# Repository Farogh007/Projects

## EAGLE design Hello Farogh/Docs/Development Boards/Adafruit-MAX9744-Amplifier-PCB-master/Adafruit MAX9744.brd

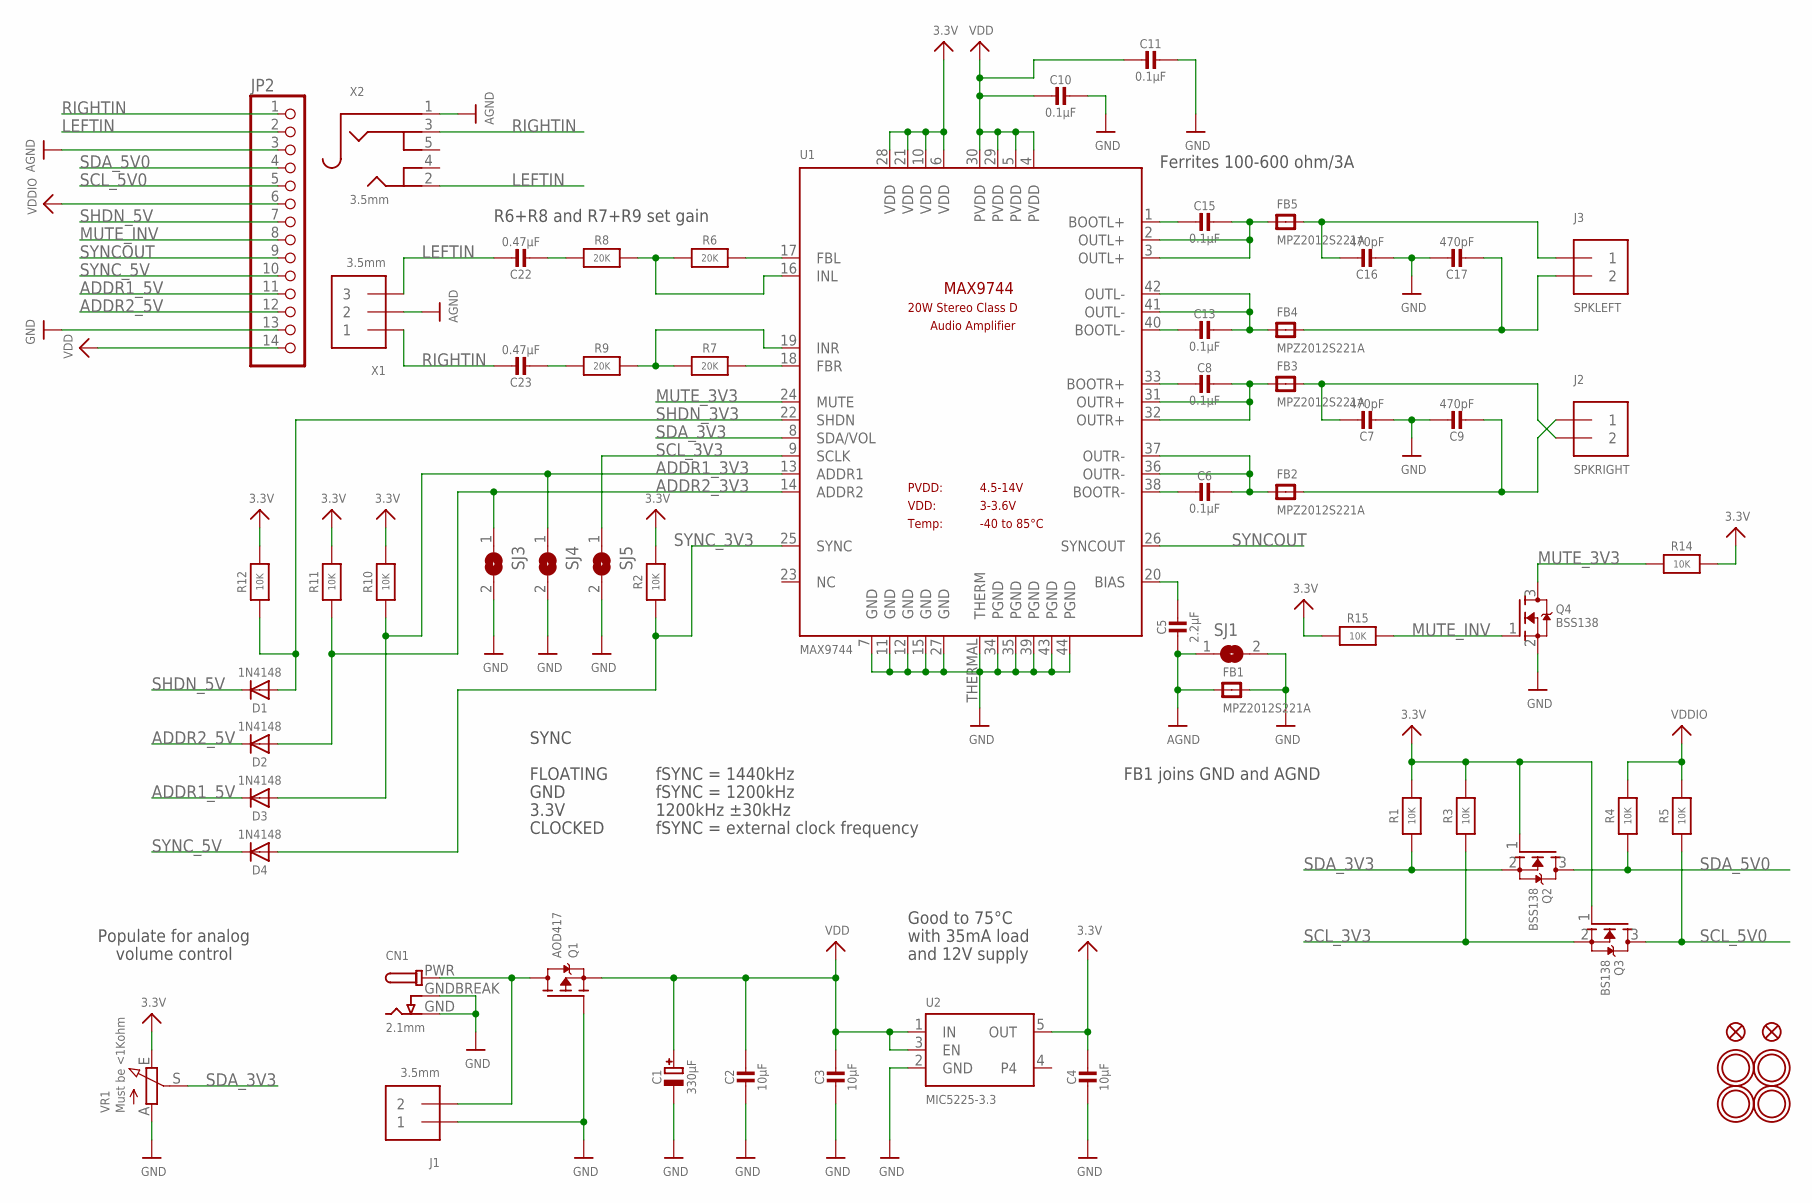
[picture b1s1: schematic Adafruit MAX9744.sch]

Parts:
C1: 330µF; CELEC_3.5MM_8MM
C2, C3, C4: 10µF; 0805-NO
C5: 2.2µF; 0805-NO
C6, C8, C10, C11, C13, C15: 0.1µF; 0805-NO
C7, C9, C16, C17: 470pF; 0805-NO
C22, C23: 0.47µF; 0805-NO
CN1: 2.1mm; DCJACK_2MM_SMT
D1, D2, D3, D4: 1N4148; SOD-323
FB1, FB2, FB3, FB4, FB5: MPZ2012S221A; _0805
FID1, FID2: FIDUCIAL""; FIDUCIAL_1MM
J1: 3.5mm; TERMBLOCK_1X2-3.5MM
J2: SPKRIGHT; TERMBLOCK_1X2-3.5MM
J3: SPKLEFT; TERMBLOCK_1X2-3.5MM
JP2: HEADER-1X14; 1X14_ROUND70
Q1: AOD417; TO252
Q2, Q4: BSS138; SOT23-WIDE
Q3: BS138; SOT23-WIDE
R1, R3, R4, R5, R12: 10K; 0805-NO
R2, R10, R11, R14, R15: 10K; _0805MP
R6, R7, R8, R9: 20K; 0805-NO
SJ1, SJ3, SJ4, SJ5: SOLDERJUMPER; SOLDERJUMPER_ARROW_NOPASTE
U1: MAX9744; TQFN44_7MM
U2: MIC5225-3.3; SOT23-5
U$29, U$38, U$39, U$40: MOUNTINGHOLE2.5_THICK; MOUNTINGHOLE_2.5_PLATED_THICK
VR1: Must be <1Kohm; TRIMPOT_100MILPTH
X1: 3.5mm; TERMBLOCK_1X3-3.5MM
X2: 3.5mm; 4UCONN_19269

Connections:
3.3V: C4.1, Q2.1 (G), Q3.1 (G), R1.2, R2.2, R3.2, R10.2, R11.2, R12.2, R14.2, R15.1, U1.6 (VDD), U1.10 (VDD), U1.21 (VDD), U1.28 (VDD), U2.5 (OUT), VR1.E
ADDR1_3V3: D3.A, R10.1, SJ4.1, U1.13 (ADDR1)
ADDR1_5V: D3.C, JP2.11
ADDR2_3V3: D2.A, R11.1, SJ3.1, U1.14 (ADDR2)
ADDR2_5V: D2.C, JP2.12
AGND: C5.2, FB1.1, JP2.3, SJ1.1, X1.2, X2.1
GND: C1.-, C2.2, C3.2, C4.2, C7.2, C9.1, C10.1, C11.1, C16.2, C17.1, CN1.GND, CN1.GNDBREAK, FB1.2, J1.1, JP2.13, Q1.1 (G), Q4.2 (S), SJ1.2, SJ3.2, SJ4.2, SJ5.2, U1.7 (GND), U1.11 (GND), U1.12 (GND), U1.15 (GND), U1.27 (GND), U1.34 (PGND), U1.35 (PGND), U1.39 (PGND), U1.43 (PGND), U1.44 (PGND), U1.THERMAL (THERM), U2.2 (GND), VR1.A
LEFTIN: C22.1, JP2.2, X1.3, X2.2
MUTE_3V3: Q4.3 (D), R14.1, U1.24 (MUTE)
MUTE_INV: JP2.8, Q4.1 (G), R15.2
unnamed: CN1.PWR, J1.2, Q1.3 (D)
unnamed: C5.1, U1.20 (BIAS)
unnamed: C6.2, U1.38 (BOOTR-)
unnamed: C6.1, FB2.1, U1.36 (OUTR-), U1.37 (OUTR-)
unnamed: C8.2, U1.33 (BOOTR+)
unnamed: C8.1, FB3.1, U1.31 (OUTR+), U1.32 (OUTR+)
unnamed: C7.1, FB3.2, J2.2
unnamed: C9.2, FB2.2, J2.1
unnamed: C13.1, FB4.1, U1.41 (OUTL-), U1.42 (OUTL-)
unnamed: C15.1, FB5.1, U1.2 (OUTL+), U1.3 (OUTL+)
unnamed: C16.1, FB5.2, J3.1
unnamed: C17.2, FB4.2, J3.2
unnamed: C15.2, U1.1 (BOOTL+)
unnamed: C13.2, U1.40 (BOOTL-)
unnamed: R6.2, U1.17 (FBL)
unnamed: R7.2, U1.18 (FBR)
unnamed: R6.1, R8.2, U1.16 (INL)
unnamed: R7.1, R9.2, U1.19 (INR)
unnamed: C22.2, R8.1
unnamed: C23.2, R9.1
RIGHTIN: C23.1, JP2.1, X1.1, X2.3
SCL_3V3: Q3.2 (S), R3.1, SJ5.1, U1.9 (SCLK)
SCL_5V0: JP2.5, Q3.3 (D), R5.1
SDA_3V3: Q2.2 (S), R1.1, U1.8 (SDA/VOL), VR1.S
SDA_5V0: JP2.4, Q2.3 (D), R4.1
SHDN_3V3: D1.A, R12.1, U1.22 (SHDN)
SHDN_5V: D1.C, JP2.7
SYNCOUT: JP2.9, U1.26 (SYNCOUT)
SYNC_3V3: D4.A, R2.1, U1.25 (SYNC)
SYNC_5V: D4.C, JP2.10
VDD: C1.+, C2.1, C3.1, C10.2, C11.2, JP2.14, Q1.2 (S), U1.4 (PVDD), U1.5 (PVDD), U1.29 (PVDD), U1.30 (PVDD), U2.1 (IN), U2.3 (EN)
VDDIO: JP2.6, R4.2, R5.2

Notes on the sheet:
Good to 75°C
with 35mA load
and 12V supply
FB1 joins GND and AGND
SYNC
FLOATING
GND
3.3V
CLOCKED
fSYNC = 1200kHz
fSYNC = 1440kHz
1200kHz ±30kHz
fSYNC = external clock frequency
R6+R8 and R7+R9 set gain
Ferrites 100-600 ohm/3A
Populate for analog
volume control

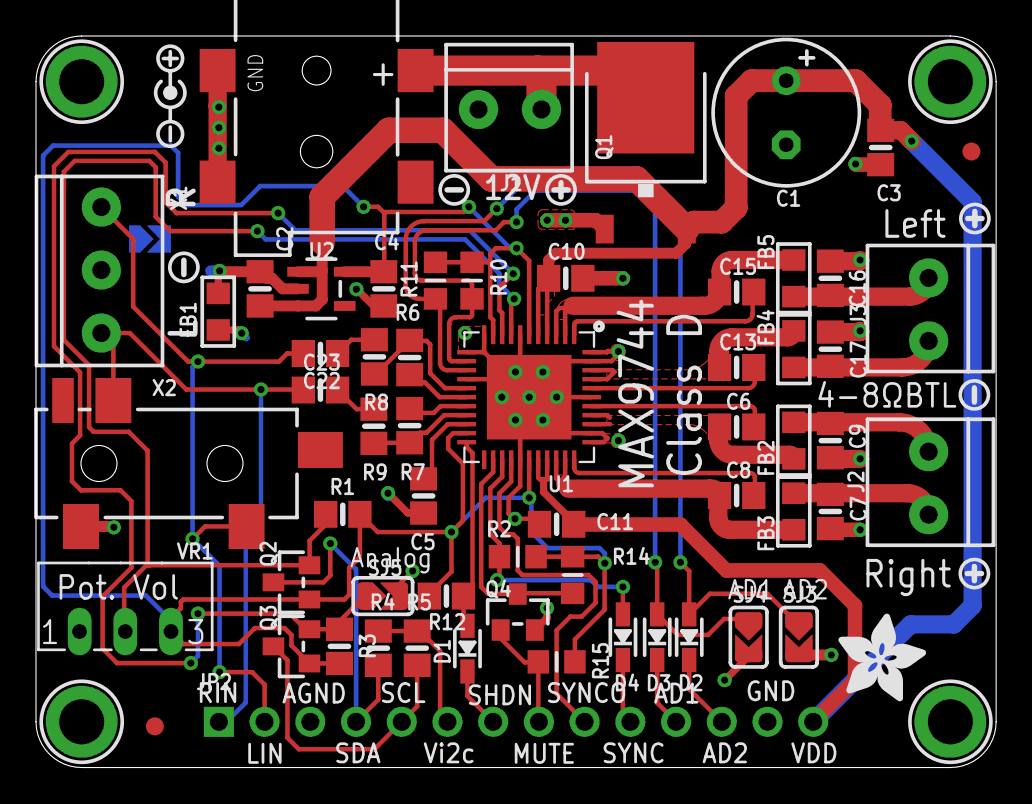
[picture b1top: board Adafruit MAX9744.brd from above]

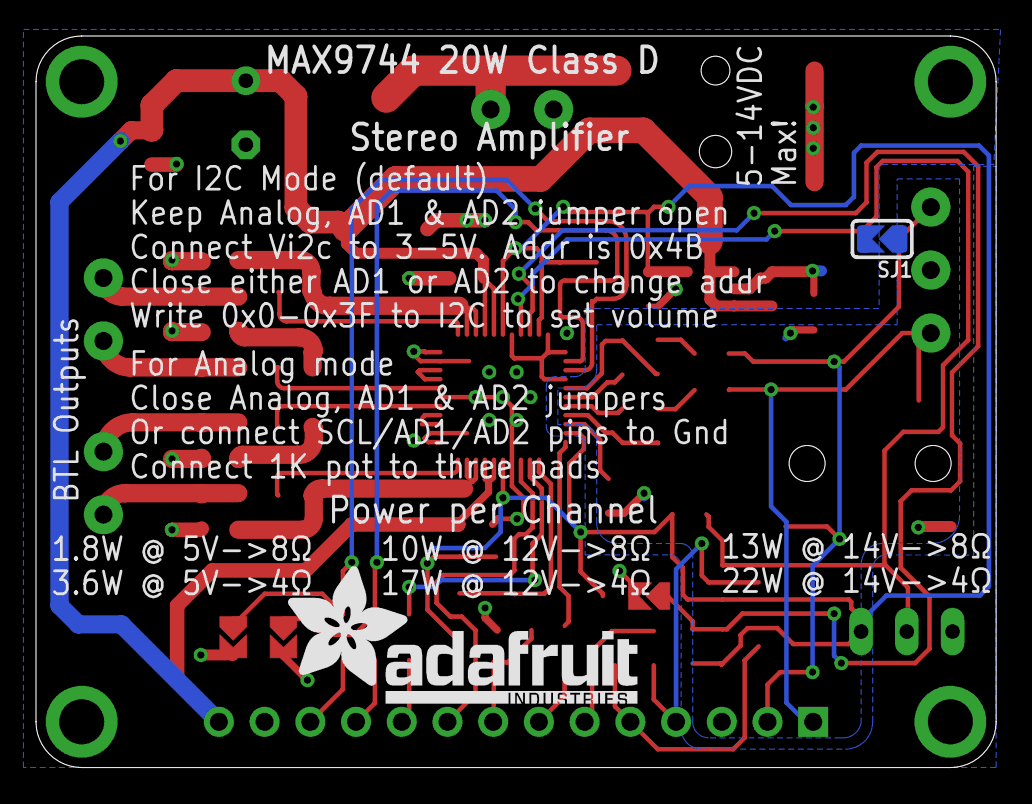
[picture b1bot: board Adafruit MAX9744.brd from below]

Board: 2 copper layers, 53.3 x 40.6 mm, 73 parts (2 on the bottom side), 42 nets.

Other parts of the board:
U$28: ADAFRUIT_TEXT_20MM
U$32: ADAFRUIT_5MM
U$41: ICON_POSITIVE_CENTER-M
U$42, U$50, U$52: ICON_PLUS
U$43, U$47, U$51: ICON_MINUS

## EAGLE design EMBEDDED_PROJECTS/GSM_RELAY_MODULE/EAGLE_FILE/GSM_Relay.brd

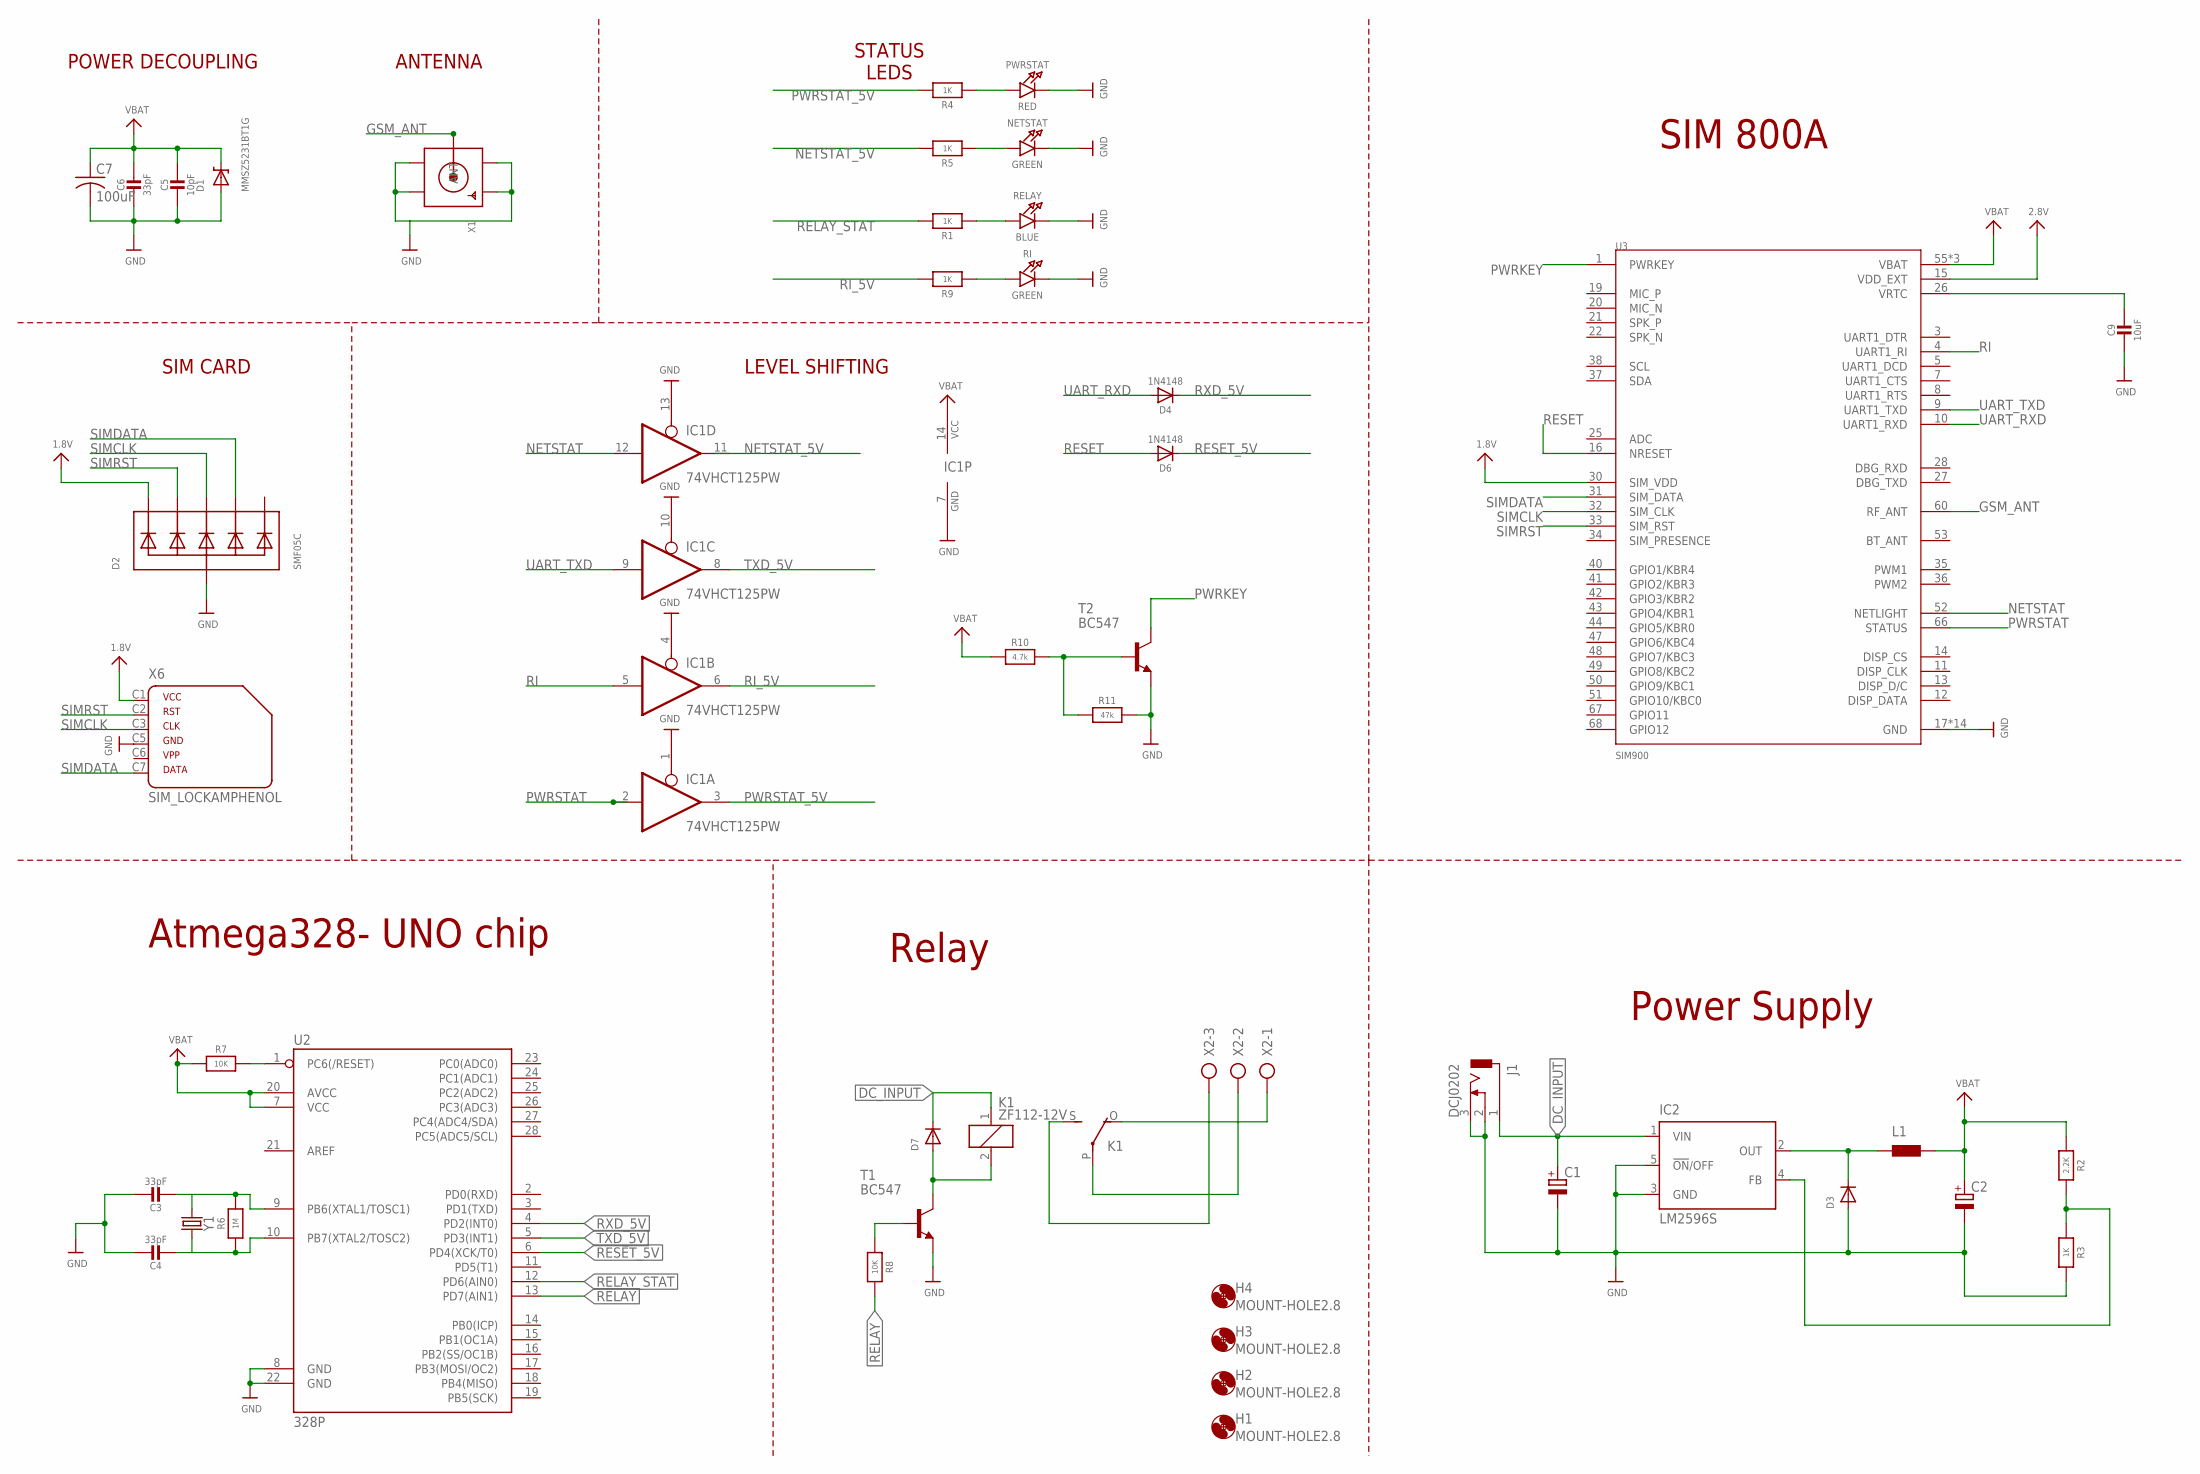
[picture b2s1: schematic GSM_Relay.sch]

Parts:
C1, C2: CPOL-EUE; PANASONIC_E
C3, C4, C6: 33pF; 0805-NO
C5: 10pF; 0805-NO
C7: 100uF; C1210
C9: 10uF; 0805-NO
D1: MMSZ5231BT1G; SOD-123
D2: SMF05C; SOT363
D3, D7: DIODESMA; SMADIODE
D4, D6: 1N4148; SOD-323
H1, H2, H3, H4: MOUNT-HOLE2.8; 2,8
IC1: 74VHCT125PW; TSSOP14
IC2: LM2596S; TO263-5
J1: DCJ0202
K1: ZF112-12V; ZF112
L1: PIS4720
NETSTAT: GREEN; CHIPLED_0805_NOOUTLINE
PWRSTAT: RED; CHIPLED_0805_NOOUTLINE
R1, R3, R4, R5, R9: 1K; 0805-NO
R2: 2.2K; 0805-NO
R6: 1M; 0805-NO
R7, R8: 10K; 0805-NO
R10: 4.7k; 0805-NO
R11: 47k; 0805-NO
RELAY: BLUE; CHIPLED_0805_NOOUTLINE
RI: GREEN; CHIPLED_0805_NOOUTLINE
T1, T2: BC547; TO92-EBC-OVAL
U2: 328P; DIP28
U3: SIM900; QFN100P2400X2400X300-68N
X1: SMACONNECTOR; SMA90_DIP
X2: AK300/3
X6: SIM_LOCKAMPHENOL; C707_10M006_512_2
Y1: CRYSTALPTH-HC49UV; HC49U

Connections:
1.8V: D2.1 (C1), U3.30 (SIM_VDD), X6.C1 (1)
2.8V: U3.15 (VDD_EXT)
DC_INPUT: C1.+, D7.C, IC2.1 (VIN), J1.1, K1.1
FEEDBACK: IC2.4 (FB), R2.2, R3.1
GND: C1.-, C2.-, C3.1, C4.1, C5.2, C6.2, C7.2, C9.2, D1.A, D2.2 (A), D3.A, IC1.1 (OE), IC1.4 (OE), IC1.7 (GND), IC1.10 (OE), IC1.13 (OE), IC2.3 (GND), IC2.5 (!ON!/OFF), J1.2, J1.3, NETSTAT.C, PWRSTAT.C, R3.2, R11.2, RELAY.C, RI.C, T1.E, T2.E, U2.8 (GND), U2.22 (GND), U3.17 (GND), U3.18 (GND), U3.29 (GND), U3.39 (GND), U3.45 (GND), U3.46 (GND), U3.54 (GND), U3.58 (GND), U3.59 (GND), U3.61 (GND), U3.62 (GND), U3.63 (GND), U3.64 (GND), U3.65 (GND), X1.GND1, X1.GND2, X1.GND3, X1.GND4, X6.C5 (4)
GSM_ANT: U3.60 (RF_ANT), X1.ANTENNA (ANT)
unnamed: R1.1, RELAY.A
unnamed: D7.A, K1.2, T1.C
unnamed: R8.1, T1.B
unnamed: PWRSTAT.A, R4.1
unnamed: D3.C, IC2.2 (OUT), L1.P$1
unnamed: C3.2, R6.2, U2.9 (PB6(XTAL1/TOSC1)), Y1.1
unnamed: C4.2, R6.1, U2.10 (PB7(XTAL2/TOSC2)), Y1.2
unnamed: R9.1, RI.A
unnamed: NETSTAT.A, R5.1
unnamed: K1.O, X2.1
unnamed: K1.P, X2.2
unnamed: R7.2, U2.1 (PC6(/RESET))
unnamed: R10.2, R11.1, T2.B
unnamed: K1.S, X2.3
NETSTAT: IC1.12 (I), U3.52 (NETLIGHT)
NETSTAT_5V: IC1.11 (O), R5.2
PWRKEY: T2.C, U3.1 (PWRKEY)
PWRSTAT: IC1.2 (I), U3.66 (STATUS)
PWRSTAT_5V: IC1.3 (O), R4.2
RELAY: R8.2, U2.13 (PD7(AIN1))
RELAY_STAT: R1.2, U2.12 (PD6(AIN0))
RESET: D6.A, U3.16 (NRESET)
RESET_5V: D6.C, U2.6 (PD4(XCK/T0))
RI: IC1.5 (I), U3.4 (UART1_RI)
RI_5V: IC1.6 (O), R9.2
RXD_5V: D4.C, U2.4 (PD2(INT0))
SIMCLK: D2.4 (C3), U3.32 (SIM_CLK), X6.C3 (3)
SIMDATA: D2.5 (C4), U3.31 (SIM_DATA), X6.C7 (6)
SIMRST: D2.3 (C2), U3.33 (SIM_RST), X6.C2 (2)
TXD_5V: IC1.8 (O), U2.5 (PD3(INT1))
UART_RXD: D4.A, U3.10 (UART1_RXD)
UART_TXD: IC1.9 (I), U3.9 (UART1_TXD)
VBAT: C2.+, C5.1, C6.1, C7.1, D1.C, IC1.14 (VCC), L1.P$2, R2.1, R7.1, R10.1, U2.7 (VCC), U2.20 (AVCC), U3.55 (VBAT), U3.56 (VBAT), U3.57 (VBAT)
VRTC: C9.1, U3.26 (VRTC)

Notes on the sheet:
ANTENNA
POWER DECOUPLING
SIM CARD
LEVEL SHIFTING
STATUS LEDS
SIM 800A
Power Supply
Relay
Atmega328- UNO chip

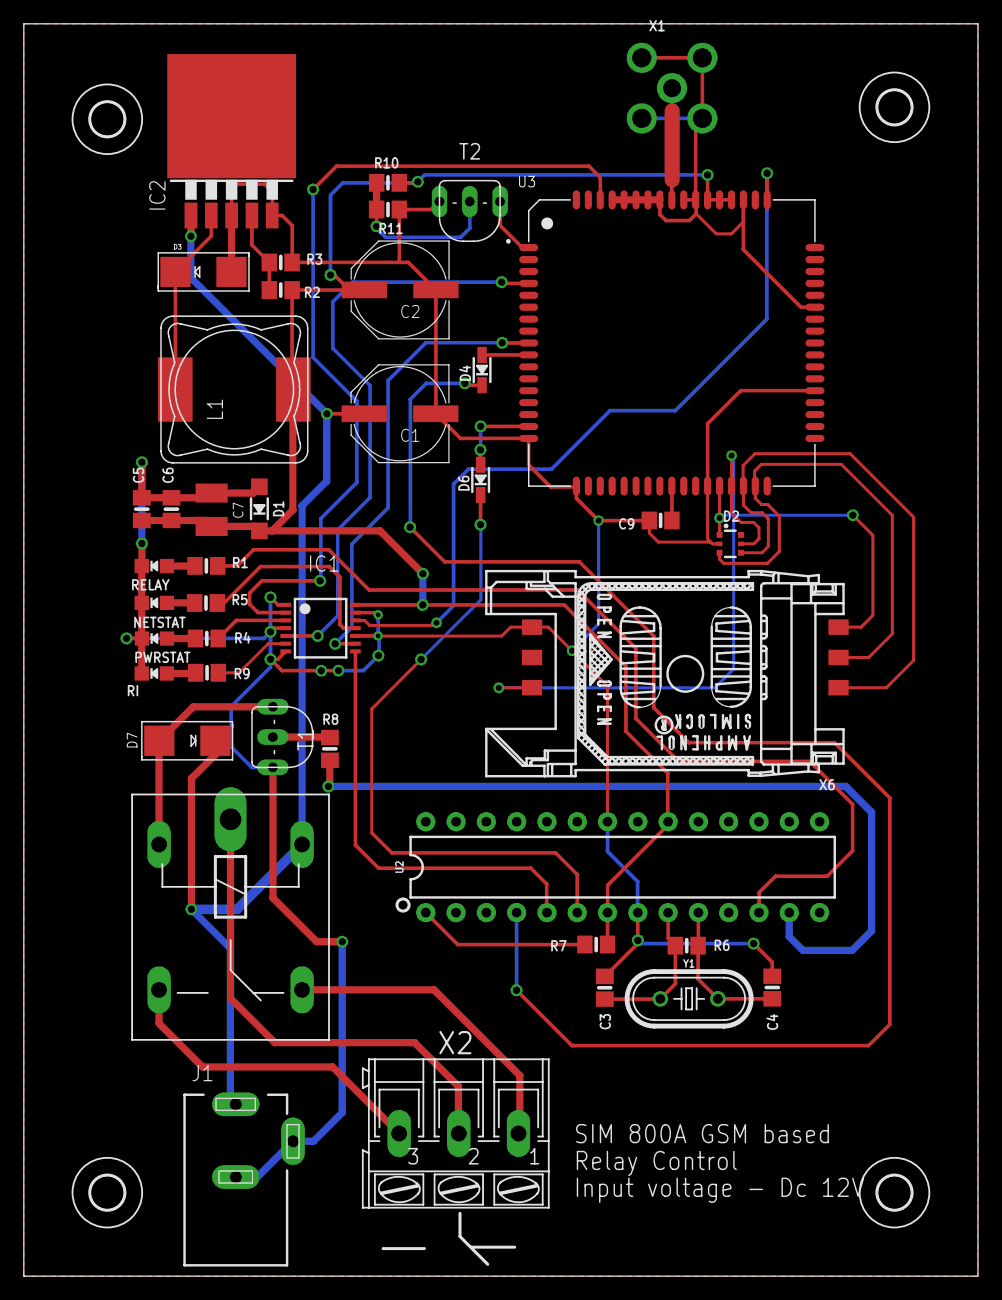
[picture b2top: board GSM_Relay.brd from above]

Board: 2 copper layers, 80.0 x 105.0 mm, 46 parts (0 on the bottom side), 39 nets.

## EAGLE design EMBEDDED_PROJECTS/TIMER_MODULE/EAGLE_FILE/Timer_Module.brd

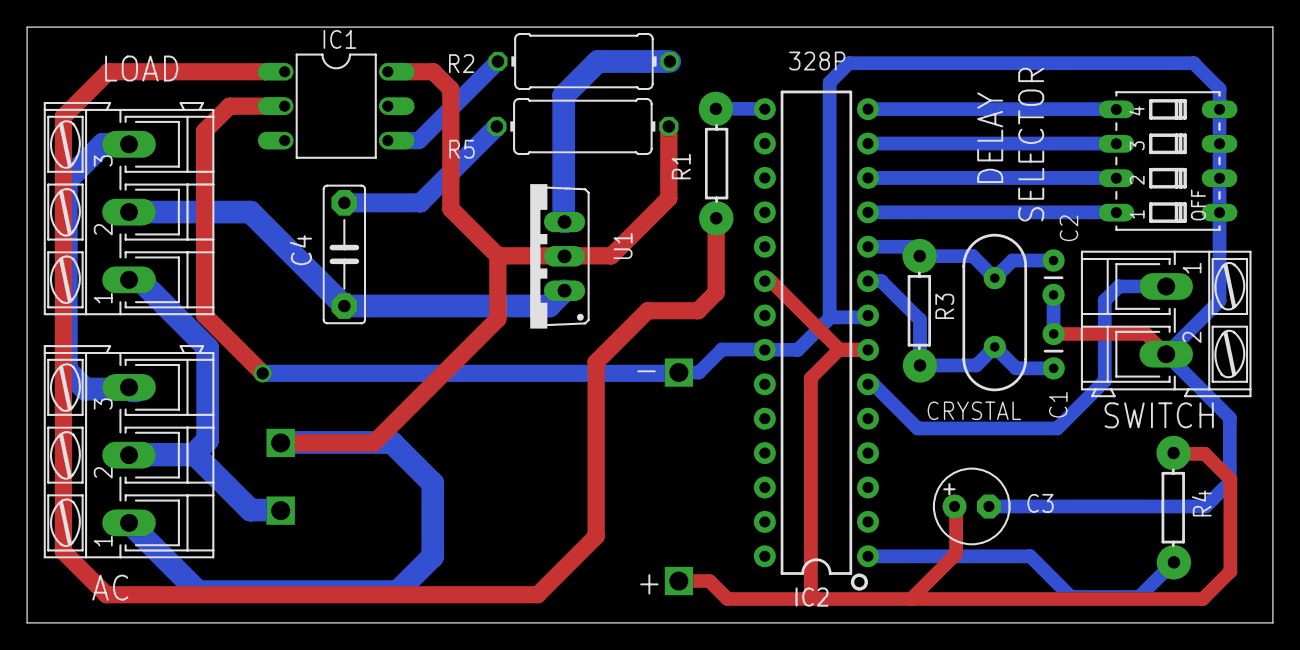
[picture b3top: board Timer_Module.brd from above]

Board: 2 copper layers, 92.0 x 44.0 mm, 18 parts (0 on the bottom side), 19 nets.

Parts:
AC_SUPPLY: AK300/3
C1, C2: 22pF; CAP-PTH-2.54
C3: 100uF; E2,5-6
C4: 10nF; C7.5B3
CRYSTAL: 16MHz; HC49US
HKLP1: HKLPM01
IC1: MOC3031M; DIL06
IC2: 328P; DIP28
LOAD: AK300/3
R1: 1k; AXIAL-0.3
R2: 470E; 0411/12
R3: 1m; AXIAL-0.3
R4: 10k; AXIAL-0.3
R5: 39E; 0411/12
SW: DIP04S
SWITCH: AK300/2
U1: BT138-V; TO220BV

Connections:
5V: C3.+, HKLP1.P$4, IC2.7, IC2.20, R4.P$2
AC_LIVE: AC_SUPPLY.1, HKLP1.P$1, IC1.6, R5.2, U1.T2
AC_NEUTRAL: AC_SUPPLY.2, HKLP1.P$2, LOAD.1
GND: C1.1, C2.1, C3.-, HKLP1.P$3, IC1.2, IC2.8, IC2.22, SW.1, SW.2, SW.3, SW.4, SWITCH.2
unnamed: C1.2, CRYSTAL.2, IC2.9, R3.P$1
unnamed: IC1.4, R2.2
unnamed: R2.1, U1.G
unnamed: C4.1, LOAD.2, U1.T1
unnamed: IC1.1, R1.P$2
unnamed: C2.2, CRYSTAL.1, IC2.10, R3.P$2
unnamed: IC2.1, R4.P$1
unnamed: C4.2, R5.1
S$1: IC2.14, SW.5
S$2: IC2.13, SW.6
S$3: IC2.12, SW.7
S$4: IC2.11, SW.8
S$5: AC_SUPPLY.3, LOAD.3
TRIGGER: IC2.15, R1.P$1
TRIG_SWITCH: IC2.6, SWITCH.1

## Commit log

2018-08-28 QT Projects
2018-08-30 GSM Module
2018-08-30 Organised Files
2018-08-30 Schematics
2018-09-11 Blog2_Timer
2019-08-27 Hello Farogh
2019-09-07 Logger

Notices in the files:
parts and their libraries:
microbuilder: This work is placed in the public domain, and may be freely used for commercial and non-commercial work with the following conditions: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
SparkFun-IC-Microcontroller: Licensing: Creative Commons ShareAlike 4.0 International - https://creativecommons.org/licenses/by-sa/4.0
